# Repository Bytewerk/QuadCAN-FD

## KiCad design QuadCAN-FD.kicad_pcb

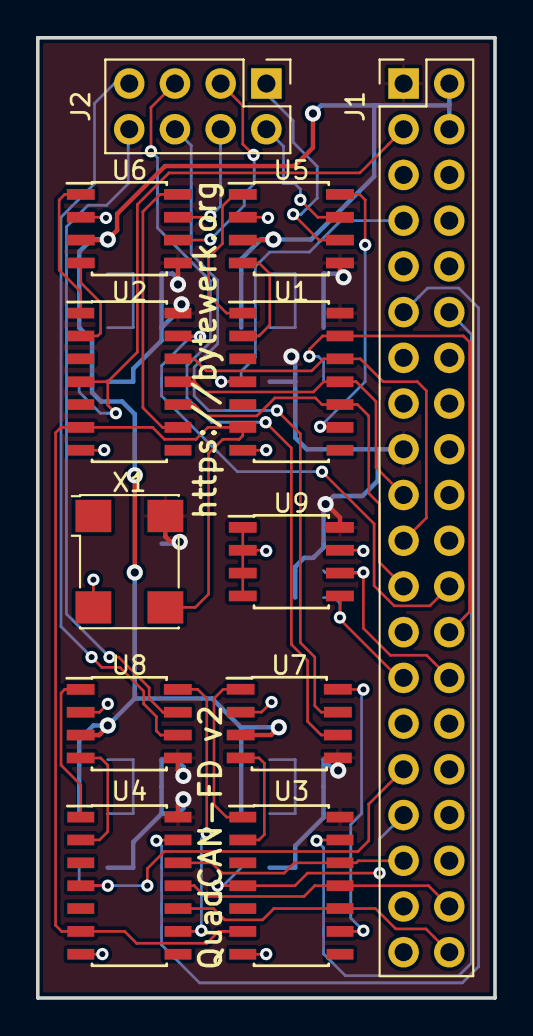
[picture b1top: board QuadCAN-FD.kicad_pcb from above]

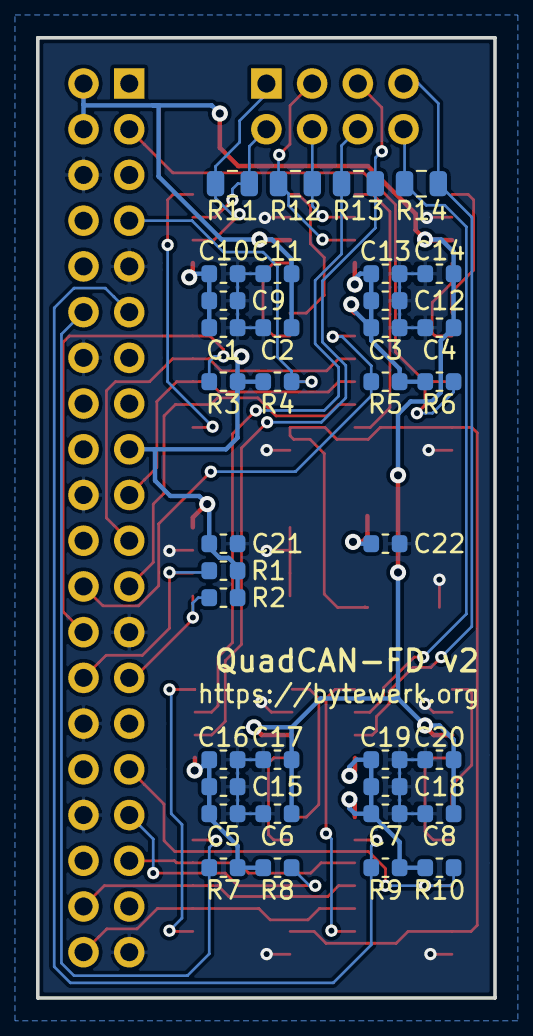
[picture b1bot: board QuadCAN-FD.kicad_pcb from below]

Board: 2 copper layers, 25.4 x 53.3 mm, 48 parts (36 on the bottom side), 40 nets.

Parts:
C1, C2, C3, C4, C5, C6, C7, C8: 1uF; C_0603_1608Metric
C9, C10, C11, C12, C13, C14, C15, C16, C17, C18, C19, C20, C21, C22: 100nF; C_0603_1608Metric
J1: Raspberry_Pi_2_3; PinHeader_2x20_P2.54mm_Vertical
J2: Conn_02x04_Odd_Even; PinHeader_2x04_P2.54mm_Vertical
R1, R2: 3K9; R_0603_1608Metric
R3, R4, R5, R6, R7, R8, R9, R10: 10K; R_0603_1608Metric
R11, R12, R13, R14: dnp; C_0805_2012Metric
U1, U2, U3, U4: MCP2517FD-xSL; SOIC-14_3.9x8.7mm_P1.27mm
U5, U6, U7, U8: TJA1049T-3; SOIC-8_3.9x4.9mm_P1.27mm
U9: AT24CS32-SSHM; SOIC-8_3.9x4.9mm_P1.27mm
X1: ASV-20MHz; Oscillator_SMD_Abracon_ASV-4Pin_7.0x5.1mm

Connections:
+3V3: C1.1, C3.1, C5.1, C7.1, C9.1, C10.1, C12.1, C13.1, C15.1, C16.1, C18.1, C19.1, C21.1, C22.1, J1.1, J1.17, R1.1, R2.1, R3.1, R4.1, R5.1, R6.1, R7.1, R8.1, R9.1, R10.1, U1.14, U2.14, U3.14, U4.14, U5.5, U6.5, U7.5, U8.5, U9.8, X1.4
+5V: C2.1, C4.1, C6.1, C8.1, C11.1, C14.1, C17.1, C20.1, J1.2, J1.4, U5.3, U6.3, U7.3, U8.3
CAN0_H: J2.2, R11.1, U5.7
CAN0_L: J2.1, R11.2, U5.6
CAN1_H: J2.4, R12.1, U6.7
CAN1_L: J2.3, R12.2, U6.6
CAN2_H: J2.6, R13.1, U7.7
CAN2_L: J2.5, R13.2, U7.6
CAN3_H: J2.8, R14.1, U8.7
CAN3_L: J2.7, R14.2, U8.6
CLK-20MHz: U1.6, U2.6, U3.6, U4.6, X1.3
GND: C1.2, C2.2, C3.2, C4.2, C5.2, C6.2, C7.2, C8.2, C9.2, C10.2, C11.2, C12.2, C13.2, C14.2, C15.2, C16.2, C17.2, C18.2, C19.2, C20.2, C21.2, C22.2, J1.6, J1.9, J1.14, J1.20, J1.25, J1.30, J1.34, J1.39, U1.7, U2.7, U3.7, U4.7, U5.2, U6.2, U7.2, U8.2, U9.1, U9.2, U9.3, U9.4, U9.7, X1.2
ID_SC: J1.28, R1.2, U9.6
ID_SD: J1.27, R2.2, U9.5
MCP0_INT: J1.7, R4.2, U1.4
MCP1_INT: J1.3, R6.2, U2.4
MCP2_INT: J1.33, R8.2, U3.4
MCP3_INT: J1.31, R10.2, U4.4
unnamed: U1.1, U5.1
unnamed: U1.2, U5.4
unnamed: U1.9, U5.8
unnamed: U2.1, U6.1
unnamed: U2.2, U6.4
unnamed: U2.9, U6.8
unnamed: U3.1, U7.1
unnamed: U3.2, U7.4
unnamed: U3.9, U7.8
unnamed: U4.1, U8.1
unnamed: U4.2, U8.4
unnamed: U4.9, U8.8
SPI0_CS0: J1.26, R3.2, U1.13
SPI0_CS1: J1.24, R5.2, U2.13
SPI0_MISO: J1.21, U1.12, U2.12
SPI0_MOSI: J1.19, U1.11, U2.11
SPI0_SCK: J1.23, U1.10, U2.10
SPI1_CS0: J1.12, R7.2, U3.13
SPI1_CS1: J1.11, R9.2, U4.13
SPI1_MISO: J1.35, U3.12, U4.12
SPI1_MOSI: J1.38, U3.11, U4.11
SPI1_SCK: J1.40, U3.10, U4.10

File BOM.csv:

"Id";"Designator";"Package";"Quantity";"Designation";"Supplier and ref";
1;"C22,C9,C10,C11,C12,C13,C14,C15,C16,C17,C18,C19,C20,C21";"C_0603_1608Metric";14;"100nF";;;
2;"R12,R13,R11,R14";"C_0805_2012Metric";4;"dnp";;;
3;"U9";"SOIC-8_3.9x4.9mm_P1.27mm";1;"AT24CS32-SSHM";;;
4;"R5,R6,R7,R8,R9,R10,R4,R3";"R_0603_1608Metric";8;"10K";;;
5;"R2,R1";"R_0603_1608Metric";2;"3K9";;;
6;"X1";"Oscillator_SMD_Abracon_ASV-4Pin_7.0x5.1mm";1;"ASV-20MHz";;;
7;"C1,C2,C3,C4,C5,C6,C7,C8";"C_0603_1608Metric";8;"1uF";;;
8;"J1";"PinHeader_2x20_P2.54mm_Vertical";1;"Raspberry_Pi_2_3";;;
9;"J2";"PinHeader_2x04_P2.54mm_Vertical";1;"Conn_02x04_Odd_Even";;;
10;"U1,U2,U3,U4";"SOIC-14_3.9x8.7mm_P1.27mm";4;"MCP2517FD-xSL";;;
11;"U5,U6,U7,U8";"SOIC-8_3.9x4.9mm_P1.27mm";4;"TJA1049T-3";;;

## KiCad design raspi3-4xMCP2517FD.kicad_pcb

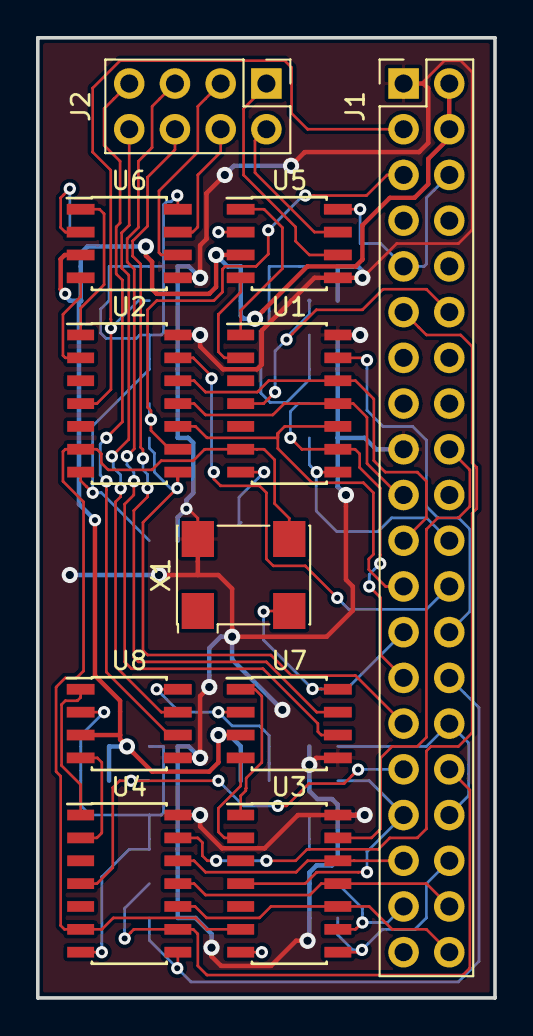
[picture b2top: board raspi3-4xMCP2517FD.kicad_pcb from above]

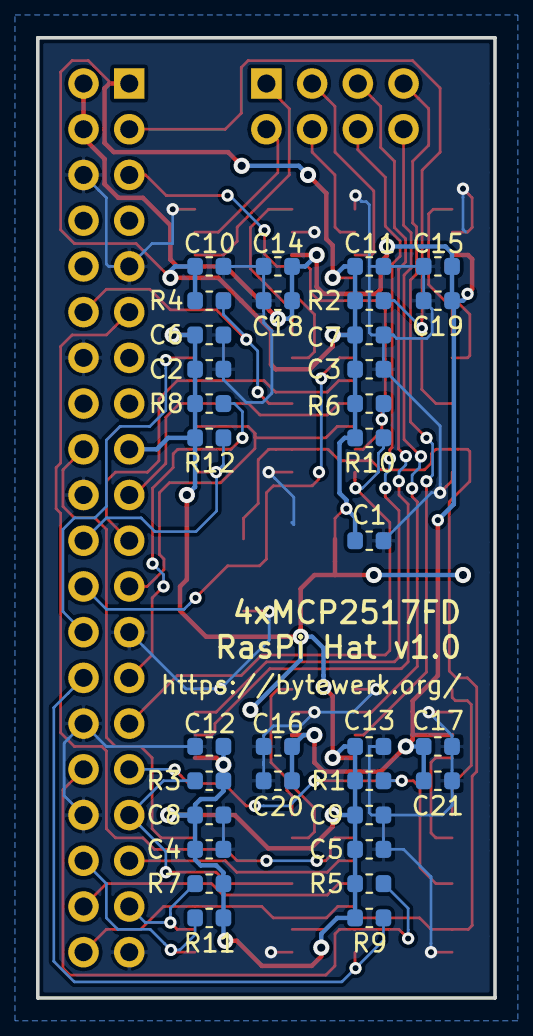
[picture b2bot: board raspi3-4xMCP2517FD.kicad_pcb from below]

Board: 2 copper layers, 25.4 x 53.3 mm, 44 parts (33 on the bottom side), 42 nets.

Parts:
C1, C6, C7, C8, C9, C10, C11, C12, C13, C14, C15, C16, C17: 100nF; C_0603_1608Metric
C2, C3, C4, C5, C18, C19, C20, C21: 1uF; C_0603_1608Metric
J1: Raspberry_Pi_2_3; PinHeader_2x20_P2.54mm_Vertical
J2: Conn_02x04_Odd_Even; PinHeader_2x04_P2.54mm_Vertical
R1, R2, R3, R4, R5, R6, R7, R8, R9, R10, R11, R12: 10K; R_0603_1608Metric
U1, U2, U3, U4: MCP2517FD-xSL; SOIC-14_3.9x8.7mm_P1.27mm
U5, U6, U7, U8: TJA1049T-3; SOIC-8_3.9x4.9mm_P1.27mm
X1: ASV-20MHz; Oscillator_SMD_Abracon_ASV-4Pin_7.0x5.1mm

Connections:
+3V3: C1.1, C2.1, C3.1, C4.1, C5.1, C6.1, C7.1, C8.1, C9.1, C10.1, C11.1, C12.1, C13.1, J1.1, J1.17, R1.1, R2.1, R3.1, R4.1, R5.1, R6.1, R7.1, R8.1, R9.1, R10.1, R11.1, R12.1, U1.14, U2.14, U3.14, U4.14, U5.5, U6.5, U7.5, U8.5, X1.4
+5V: C14.1, C15.1, C16.1, C17.1, C18.1, C19.1, C20.1, C21.1, J1.2, J1.4, U5.3, U6.3, U7.3, U8.3
CAN0_H: J2.2, U5.7
CAN0_L: J2.1, U5.6
CAN1_H: J2.4, U6.7
CAN1_L: J2.3, U6.6
CAN2_H: J2.6, U7.7
CAN2_L: J2.5, U7.6
CAN3_H: J2.8, U8.7
CAN3_L: J2.7, U8.6
CLK-20MHz: U1.6, U2.6, U3.6, U4.6, X1.3
GND: C1.2, C2.2, C3.2, C4.2, C5.2, C6.2, C7.2, C8.2, C9.2, C10.2, C11.2, C12.2, C13.2, C14.2, C15.2, C16.2, C17.2, C18.2, C19.2, C20.2, C21.2, J1.6, J1.9, J1.14, J1.20, J1.25, J1.30, J1.34, J1.39, U1.7, U2.7, U3.7, U4.7, U5.2, U5.8, U6.2, U6.8, U7.2, U7.8, U8.2, U8.8, X1.2
MCP0_INT: J1.12, R4.2, U1.4
MCP0_INT0: J1.27, R8.2, U1.9
MCP0_INT1: J1.22, R12.2, U1.8
MCP1_INT: J1.3, R2.2, U2.4
MCP1_INT0: J1.5, R6.2, U2.9
MCP1_INT1: J1.29, R10.2, U2.8
MCP2_INT: J1.33, R3.2, U3.4
MCP2_INT0: J1.37, R7.2, U3.9
MCP2_INT1: J1.36, R11.2, U3.8
MCP3_INT: J1.31, R1.2, U4.4
MCP3_INT0: J1.32, R5.2, U4.9
MCP3_INT1: J1.28, R9.2, U4.8
unnamed: U1.1, U5.1
unnamed: U1.2, U5.4
unnamed: U2.1, U6.1
unnamed: U2.2, U6.4
unnamed: U3.1, U7.1
unnamed: U3.2, U7.4
unnamed: U4.1, U8.1
unnamed: U4.2, U8.4
SPI0_CS0: J1.26, U1.13
SPI0_CS1: J1.24, U2.13
SPI0_MISO: J1.21, U1.12, U2.12
SPI0_MOSI: J1.19, U1.11, U2.11
SPI0_SCK: J1.23, U1.10, U2.10
SPI1_CS0: J1.18, U3.13
SPI1_CS1: J1.11, U4.13
SPI1_MISO: J1.35, U3.12, U4.12
SPI1_MOSI: J1.38, U3.11, U4.11
SPI1_SCK: J1.40, U3.10, U4.10

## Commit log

2018-06-29 initial checkin
2018-08-31 add bom csv
2018-09-07 start raspbian support
2018-09-08 fix readme
2018-09-08 add second mcp
2018-09-09 3 devices working!
2018-09-10 make v2
2018-09-10 rename project
2018-09-11 use latest driver
2018-09-11 4 MCPs working!
2018-09-12 add udev rules file for consistant device names
